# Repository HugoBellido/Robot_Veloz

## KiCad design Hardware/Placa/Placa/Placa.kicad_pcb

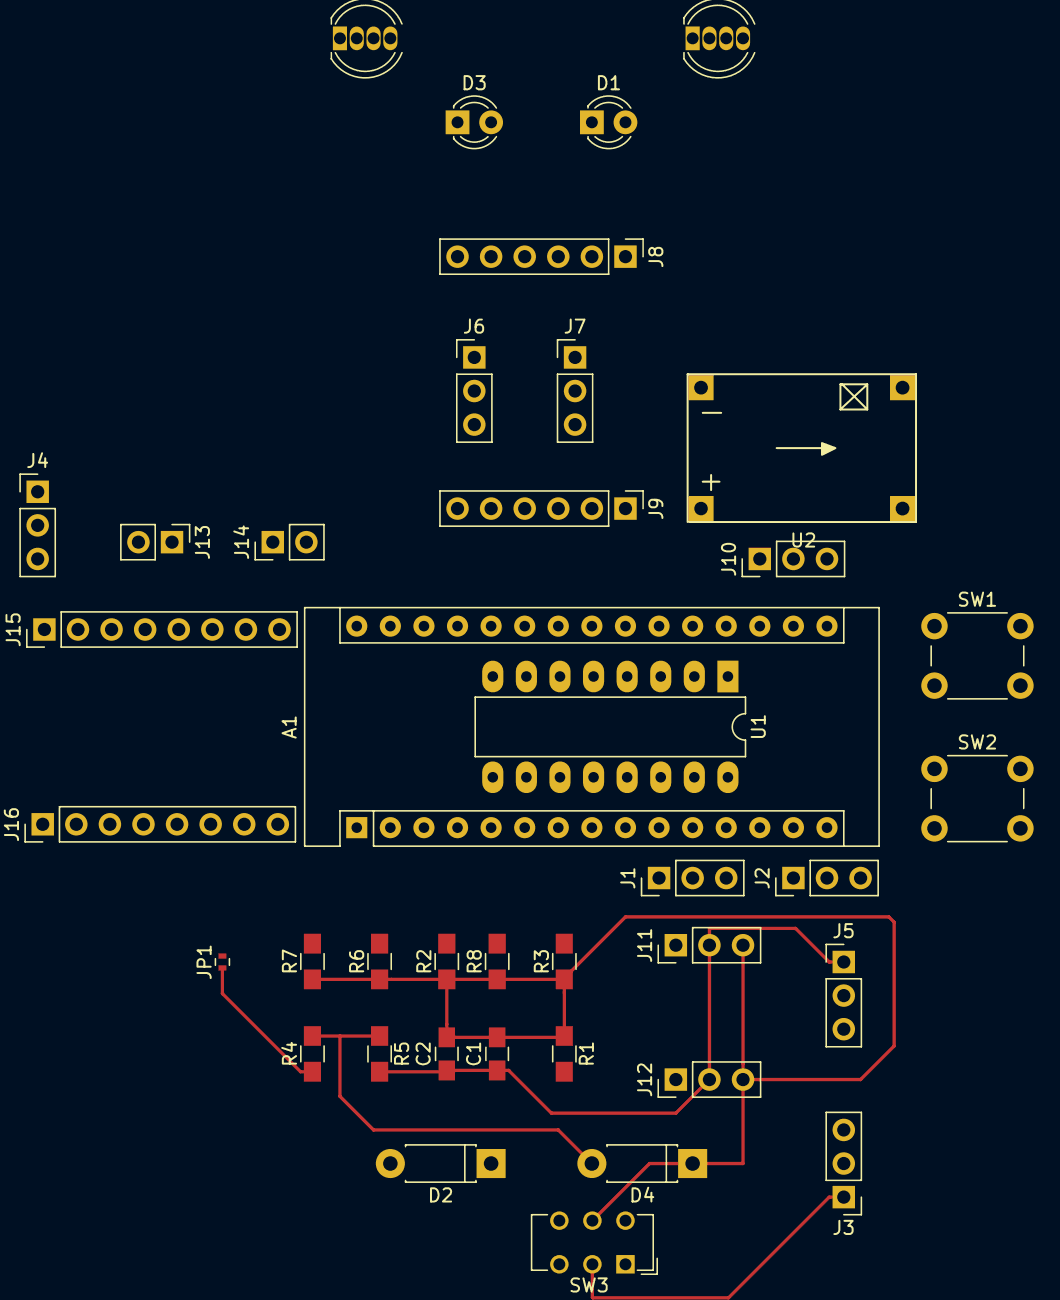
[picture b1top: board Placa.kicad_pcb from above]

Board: 2 copper layers, 39 parts (0 on the bottom side), 46 nets.

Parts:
A1: Arduino_Nano_v3.x; Arduino_Nano
C1, C2: C; C_0805_HandSoldering
D1, D3: LED; LED_D3.0mm
D2, D4: D_Small; D_DO-41_SOD81_P7.62mm_Horizontal
D5, D6: NeoPixel_THT; LED_D5.0mm-4
J1, J2, J3, J4, J5, J10, J11, J12: Conn_01x03; Pin_Header_Straight_1x03_Pitch2.54mm
J6, J7: Conn_01x02; Pin_Header_Straight_1x03_Pitch2.54mm
J8, J9: Conn_01x06; Pin_Header_Straight_1x06_Pitch2.54mm
J13, J14: Conn_01x02; Pin_Header_Straight_1x02_Pitch2.54mm
J15, J16: Conn_01x08; Pin_Header_Straight_1x08_Pitch2.54mm
JP1: Jumper_NO_Small; R_0402
R1, R2, R3, R4, R5, R6, R7, R8: R_Small; R_0805_HandSoldering
SW1, SW2: SW_Push; SW_PUSH_6mm
SW3: SW_DPDT_x2; SW_CuK_JS202011CQN_DPDT_Straight
U1: PCF8574; DIP-16_W7.62mm_LongPads
U2: DC-DC_BuckModule; DC-DC-MP2307

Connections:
+5V: A1.27, C1.2, C2.2, D4.1, D5.3, D6.3, J4.2, J4.3, J8.2, J9.1, J10.3, J11.3, J12.3, J15.2, R1.1, R2.1, R3.1, R6.1, R7.1, R8.1, SW3.5, U1.16, U2.3
A1: A1.20, J4.1
B1: R3.2, SW1.1, U1.11
B2: R6.2, SW2.1, U1.12
BAT: A1.19, D4.2, R4.2, R5.1
BT_RX: A1.1, J8.5
BT_TX: A1.2, D2.2
D7: A1.10, J1.1
D8: A1.11, J1.2
D9: A1.12, J1.3
D10: A1.13, J2.1
D11: A1.14, J2.2
D13: A1.16, J2.3
DIR_DER_1: J16.5, U1.9
DIR_DER_2: J16.6, U1.10
DIR_IZQ_1: J16.3, U1.6
DIR_IZQ_2: J16.2, U1.7
DIST_DCHA: A1.24, J10.1
DIST_FRONT: A1.25, J11.1
DIST_IZQ: A1.26, J12.1
GND: A1.4, A1.29, C1.1, C2.1, D5.2, D6.2, J3.3, J5.1, J5.2, J5.3, J7.2, J8.3, J9.2, J10.2, J11.2, J12.2, J15.3, J15.8, J16.8, R5.2, SW1.2, SW2.2, U1.1, U1.2, U1.3, U1.8, U2.2, U2.4
I2C_SCL: A1.8, R8.2, U1.14
I2C_SDA: A1.7, R7.2, U1.15
LED_G: D3.1, U1.4
LED_R: D1.1, U1.5
LINEA_1: A1.21, J9.3
LINEA_2: A1.22, J9.4
LINEA_3: A1.23, J9.5
LINEA_SEL: A1.15, J9.6
M_DER_+: J14.2, J15.7
M_DER_-: J14.1, J15.6
M_IZQ_+: J13.2, J15.4
M_IZQ_-: J13.1, J15.5
NEO: A1.5, D6.4
unnamed: D1.2, R1.2
unnamed: D2.1, J8.4
unnamed: D3.2, R2.2
unnamed: D5.4, D6.1
unnamed: J6.2, J7.1
unnamed: SW3.3, U2.1
PWM_DER: A1.6, J16.7
PWM_IZQ: A1.9, J16.1
STBY_MOT: J16.4, SW3.6
VBAT: J3.1, J6.1, J15.1, SW3.2
VCC: A1.30, JP1.2
VDD: JP1.1, R4.1

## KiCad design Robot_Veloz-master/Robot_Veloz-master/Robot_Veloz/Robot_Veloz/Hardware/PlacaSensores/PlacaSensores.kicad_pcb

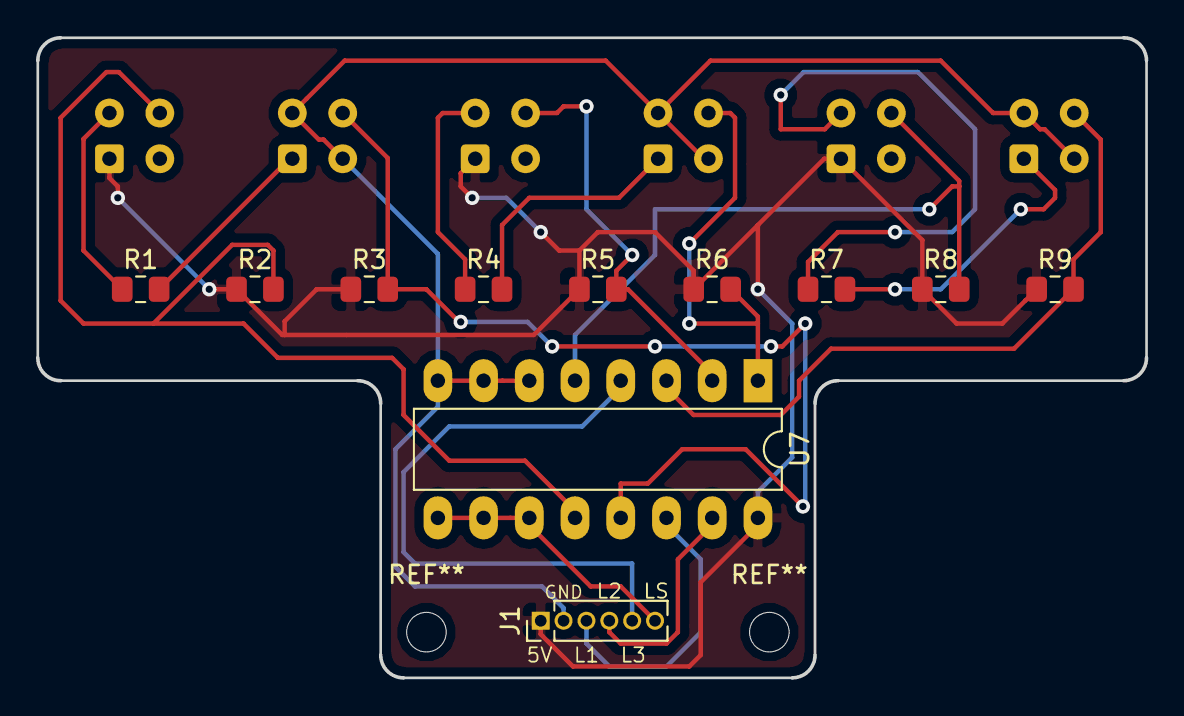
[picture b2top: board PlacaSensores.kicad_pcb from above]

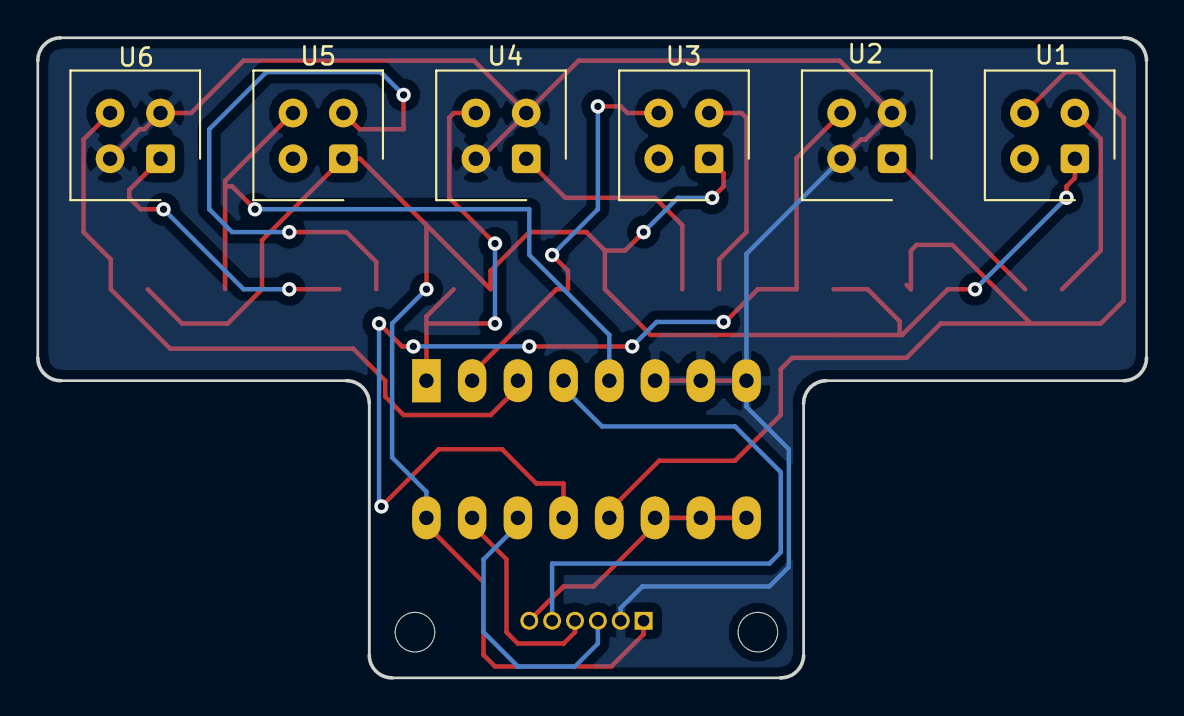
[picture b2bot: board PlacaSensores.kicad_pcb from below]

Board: 2 copper layers, 61.6 x 35.6 mm, 17 parts (6 on the bottom side), 18 nets.

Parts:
J1: Conn_01x06_Female; PinHeader_1x06_P1.27mm_Vertical
R1, R4, R7: 82; R_0805_2012Metric_Pad1.15x1.40mm_HandSolder
R2, R3, R5, R6, R8, R9: 10k; R_0805_2012Metric_Pad1.15x1.40mm_HandSolder
U1, U2, U3, U4, U5, U6: CNY70; Vishay_CNY70
U7: 4053; DIP-16_W7.62mm_LongPads

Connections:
+5V: J1.1, R2.1, R3.1, R5.1, R6.1, R8.1, R9.1, U1.1, U3.1, U5.1, U7.16
/L1: J1.3, U7.14
/L2: J1.4, U7.15
/L3: J1.5, U7.4
/LS: J1.6, U7.9, U7.10, U7.11
/S1: R2.2, U1.3, U7.12
/S2: R3.2, U2.3, U7.13
/S3: R5.2, U3.3, U7.2
/S4: R6.2, U4.3, U7.1
/S5: R8.2, U5.3, U7.5
/S6: R9.2, U6.3, U7.3
GND: J1.2, U2.2, U2.4, U4.2, U4.4, U6.2, U6.4, U7.6, U7.7, U7.8
unnamed: R1.1, U1.2
unnamed: R1.2, U2.1
unnamed: R4.1, U3.2
unnamed: R4.2, U4.1
unnamed: R7.1, U5.2
unnamed: R7.2, U6.1

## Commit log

2018-11-17 Placa Sensores
    Está casi terminada.
2018-11-24 PlacaSensores Terminada y esquema de Placa empezado
2018-12-01 ESQUEMA PLACA CASI TERMINADO
2018-12-15 esquema placa terminado
